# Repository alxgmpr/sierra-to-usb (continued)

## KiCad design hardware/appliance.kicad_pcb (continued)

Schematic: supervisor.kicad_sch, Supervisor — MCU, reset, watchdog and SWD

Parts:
C201, C202: 100nF; C_0603_1608Metric_Pad1.08x0.95mm_HandSolder; Rating 25V X7R +/-10%; 0603; Tolerance 10%; MPN CL10B104KA8NNNC; LCSC C1590
C203: 10uF; C_1206_3216Metric_Pad1.33x1.80mm_HandSolder; Rating 25V X7R +/-10%; bias margin reviewed; a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; Tolerance 10%; MPN CL31B106KBHNNNE; LCSC C89632
C204, C205: 100nF; C_0603_1608Metric_Pad1.08x0.95mm_HandSolder; Tolerance 10%; Voltage Rating 25V; MPN CL10B104KA8NNNC; LCSC C1590
J201: SWD TC2050; Tag-Connect_TC2050-IDC-FP_2x05_P1.27mm_Vertical; MPN TC2050-IDC
J202: WDT RUN jumper; Wuerth_61300211121_1x02_P2.54mm_Vertical; MPN 61300211121
R201, R202, R203: 10kR; R_0603_1608Metric_Pad0.98x0.95mm_HandSolder; Tolerance 1%; Power Rating 0.1W; MPN RC0603FR-0710KL; LCSC C98220
SW201: RESET; SW_SPST_TL3342; Contact Rating 12VDC 50mA; MPN TL3342F160QG; LCSC C2886898
U201: STM32G0B1CCT6; LQFP-48_7x7mm_P0.5mm; MPN STM32G0B1CCT6; LCSC C5270241
U202: TPS3828-33DBVR; SOT-23-5_HandSoldering; MPN TPS3828-33DBVR; LCSC C20032

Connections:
+3V3: C201.1, C202.1, C203.1, C204.1, J201.1 (VCC), R201.1, R203.1, U201.4 (VBAT), U201.5 (VREF+), U201.6 (VDD), U202.5 (V_{DD}); also elsewhere on the board
/Recovery and always-on supply/ETH_RESET_ASSERT: U201.8 (PF0); also elsewhere on the board
/Recovery and always-on supply/MODEM_OFF_ASSERT: U201.34 (PA10/PA12); also elsewhere on the board
/Recovery and always-on supply/MODEM_RESET_ASSERT: U201.33 (PA9/PA11); also elsewhere on the board
/Recovery and always-on supply/POWER_FAULT_N: U201.20 (PB1); also elsewhere on the board
/Recovery and always-on supply/SERVICE_RX: U201.14 (PA3); also elsewhere on the board
/Recovery and always-on supply/SERVICE_TX: U201.13 (PA2); also elsewhere on the board
/Recovery and always-on supply/Supervisor/MANUAL_RESET_N: R203.2, SW201.1, U202.3 (~MR)
/Recovery and always-on supply/Supervisor/MCU_NRST_N: C205.1, J201.10 (nRESET), R201.2, U201.10 (PF2), U202.1 (~RESET)
/Recovery and always-on supply/Supervisor/SWCLK: J201.4 (SWCLK), U201.36 (PA14)
/Recovery and always-on supply/Supervisor/SWDIO: J201.2 (SWDIO), U201.35 (PA13)
/Recovery and always-on supply/Supervisor/WDT_INPUT: J202.2, U202.4 (WDI)
/Recovery and always-on supply/Supervisor/WDT_KICK: J202.1, R202.1, U201.19 (PB0)
ADC_3V3_MAIN: U201.15 (PA4); also elsewhere on the board
ADC_5V_MAIN: U201.12 (PA1); also elsewhere on the board
ADC_AUX_12V: U201.11 (PA0); also elsewhere on the board
ADC_MODEM_ILM: U201.17 (PA6); also elsewhere on the board
ADC_MODEM_VCC: U201.16 (PA5); also elsewhere on the board
ADC_NTC_MODEM: U201.18 (PA7); also elsewhere on the board
ADC_NTC_POWER: U201.21 (PB2); also elsewhere on the board
GND: C201.2, C202.2, C203.2, C204.2, C205.2, J201.3 (GND), J201.5 (GND), J201.9 (GND), R202.2, SW201.2, U201.7 (VSS), U202.2 (GND); also elsewhere on the board
LED_FAULT_N: U201.39 (PD1); also elsewhere on the board
LED_PWR_N: U201.28 (PA8); also elsewhere on the board
LED_SYS_N: U201.37 (PA15); also elsewhere on the board
LED_WAN_N: U201.38 (PD0); also elsewhere on the board
MAIN3V3_GOOD: U201.44 (PB5); also elsewhere on the board
MAIN5V_GOOD: U201.46 (PB7); also elsewhere on the board
MCU_ETH_POWER_EN: U201.41 (PD3); also elsewhere on the board
MCU_HEALTH_IN: U201.1 (PC13); also elsewhere on the board
MCU_LINK_RX: U201.31 (PC7); also elsewhere on the board
MCU_LINK_TX: U201.30 (PC6); also elsewhere on the board
MCU_MAIN5V_EN: U201.45 (PB6); also elsewhere on the board
MCU_MODEM_POWER_EN: U201.40 (PD2); also elsewhere on the board
MCU_PROCESSOR_RECOVERY_ASSERT: U201.42 (PB3); also elsewhere on the board
MCU_PROCESSOR_RESET_ASSERT: U201.9 (PF1); also elsewhere on the board
MCU_PWRON_KICK: U201.43 (PB4); also elsewhere on the board
MODEM_BUCK_GOOD: U201.27 (PB15); also elsewhere on the board
MODEM_RAIL_GOOD: U201.25 (PB13); also elsewhere on the board
MODEM_SWITCH_GOOD: U201.26 (PB14); also elsewhere on the board
MON_ALERT_N: U201.2 (PC14); also elsewhere on the board
MON_I2C_SCL: U201.47 (PB8); also elsewhere on the board
MON_I2C_SDA: U201.48 (PB9); also elsewhere on the board
POE_BT_N: U201.24 (PB12); also elsewhere on the board
POE_TPH_N: U201.22 (PB10); also elsewhere on the board
POE_TPL_N: U201.23 (PB11); also elsewhere on the board

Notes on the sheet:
100nF at VDD/VREF; 10uF local bulk. No external clock required for UART/GPIO supervision.
PROGRAMMING / MANUAL RECOVERY
SUPERVISOR MCU — CONTROL ONLY
PF2 / pin 10 MUST remain NRST via option bytes. Internal BOR and IWDG enabled by protected boot firmware. PA2/PA3: USART2 AF1; PA13/PA14: SWD. UART is service only; no modem AT transport selected. Two signed app slots + protected loader planned; not implemented.
Fit RUN jumper for unattended use. Remove only for physical SWD service. WDI floats only with jumper removed.
VTref only; debugger must not power the target. Leave debug unlocked until signed-update recovery is proven. No USB data path through this MCU.
1.6s nominal watchdog; 2.93V threshold; 200ms nominal reset. Open-drain RESET directly shares MCU NRST with SWD. Verify NRST low-voltage margin across temperature before release.
EXTERNAL WATCHDOG + BROWNOUT

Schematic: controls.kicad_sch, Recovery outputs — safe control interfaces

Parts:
Q301, Q302, Q303: MMBT3904,215; SOT-23_Handsoldering; MPN MMBT3904,215
R301, R303, R305: 10kR; R_0603_1608Metric_Pad0.98x0.95mm_HandSolder; Tolerance 1%; Power Rating 0.1W; MPN RC0603FR-0710KL; LCSC C98220
R302, R304, R306, R307, R308: 100kR; R_0603_1608Metric_Pad0.98x0.95mm_HandSolder; Tolerance 1%; Power Rating 0.1W; MPN RC0603FR-07100KL; LCSC C14675

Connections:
/Recovery and always-on supply/ETH_RESET_ASSERT: R305.1; also elsewhere on the board
/Recovery and always-on supply/MODEM_OFF_ASSERT: R303.1; also elsewhere on the board
/Recovery and always-on supply/MODEM_RESET_ASSERT: R301.1; also elsewhere on the board
ETH_PERST_N: Q303.3 (C); also elsewhere on the board
GND: Q301.2 (E), Q302.2 (E), Q303.2 (E), R302.2, R304.2, R306.2, R307.2, R308.2; also elsewhere on the board
MCU_ETH_POWER_EN: R308.1; also elsewhere on the board
MCU_MODEM_POWER_EN: R307.1; also elsewhere on the board
MODEM_OFF_N: Q302.3 (C); also elsewhere on the board
MODEM_RESET_N: Q301.3 (C); also elsewhere on the board
unnamed: Q301.1 (B), R301.2, R302.1
unnamed: Q302.1 (B), R303.2, R304.1
unnamed: Q303.1 (B), R305.2, R306.1

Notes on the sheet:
INTEGRATION LIMITS
OPEN-COLLECTOR RESET / OFF — NO EXTERNAL PULL-UP TO ALWAYS-ON RAIL
POWER ENABLES — DEFAULT OFF ON MCU RESET
HIGH input asserts LOW output. Target pull-up / timing is profile-specific.
Reset outputs tolerate target pull-ups without sourcing voltage into an unpowered target. Maximum target sink current allocation: 1mA; verify low threshold with exact load. MODEM_OFF_N connects to FULL_CARD_POWER_OFF# only with a switched target-rail pull-up. Without that pull-up, the module remain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
Connect only to documented 3.3V-compatible enable inputs. The regulators / eFuses are NOT captured in this milestone.

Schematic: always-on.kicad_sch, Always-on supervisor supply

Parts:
C401: 10uF; C_1206_3216Metric_Pad1.33x1.80mm_HandSolder; Tolerance 10%; Voltage Rating 50V; MPN CL31B106KBHNNNE; LCSC C89632
C402, C403: 22uF; C_1210_3225Metric_Pad1.33x2.70mm_HandSolder; Tolerance 10%; Voltage Rating 25V; MPN CL32B226KAJNNNE; LCSC C309062
L401: 10uH; L_Coilcraft_LPS4018; MPN LPS4018-103MRC; LCSC C6127589
R401: 100kR; R_0603_1608Metric_Pad0.98x0.95mm_HandSolder; Tolerance 1%; Power Rating 0.1W; MPN RC0603FR-07100KL; LCSC C14675
U401: TPS62177DQCR; WSON-10-1EP_2x3mm_P0.5mm_EP0.84x2.4mm_ThermalVias; MPN TPS62177DQCR; LCSC C91241

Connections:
+3V3: C402.1, C403.1, L401.2, R401.1, U401.8 (~SLEEP), U401.10 (VOS); also elsewhere on the board
/Recovery and always-on supply/POWER_FAULT_N: R401.2, U401.7 (PG); also elsewhere on the board
GND: C401.2, C402.2, C403.2, U401.1 (PGND), U401.4 (NC), U401.5 (FB), U401.6 (AGND), U401.11 (PAD); also elsewhere on the board
ISO_12V: C401.1, U401.2 (VIN), U401.3 (EN); also elsewhere on the board
unnamed: L401.1, U401.9 (SW)

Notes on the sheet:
Independent supervisor supply
DRAFT: isolated 12V input; 3.3V / 0.5A output. No connection to raw PoE. EN tied to input; SLEEP tied to 3.3V for normal operation. Always on while the isolated input is present; downstream cuts must not gate this rail.
TI SLVSB35C, Figure 8 / Tables 2-3. 10uH + 2x22uF nominal. Capacitor DC bias, complete rail load and layout review remain open. Route VOS as Kelvin sense after L401; join AGND / PGND / exposed pad locally.

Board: 6 copper layers, 816 parts (202 on the bottom side), 426 nets, no tracks yet.

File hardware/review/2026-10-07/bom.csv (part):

Reference,Value,MPN,Manufacturer,Footprint,Default Assembly,Profile Rule,Datasheet,Release
J101,3.3V RAIL TEST,61300211121,Wuerth Elektronik,Recovery:Wuerth_61300211121_1x02_P2.54mm_Vertical,Fit,,https://www.we-online.com/components/products/datasheet/6130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,Engineering inventory; modem/footprint/electrical qualification pending
J102,CONTROL BOUNDARY,61301011121,Wuerth Elektronik,Recovery:Wuerth_61301011121_1x10_P2.54mm_Vertical,Fit,,https://www.we-online.com/components/products/datasheet/6130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,Engineering inventory; modem/footprint/electrical qualification pending
Q301,"MMBT3904,215","MMBT3904,215",Nexperia,Package_TO_SOT_SMD:SOT-23_Handsoldering,Fit,,https://assets.nexperia.com/documents/data-sheet/MMBT3904.pdf,Engineering inventory; modem/footprint/electrical qualification pending
Q302,"MMBT3904,215","MMBT3904,215",Nexperia,Package_TO_SOT_SMD:SOT-23_Handsoldering,Fit,,https://assets.nexperia.com/documents/data-sheet/MMBT3904.pdf,Engineering inventory; modem/footprint/electrical qualification pending
Q303,"MMBT3904,215","MMBT3904,215",Nexperia,Package_TO_SOT_SMD:SOT-23_Handsoldering,Fit,,https://assets.nexperia.com/documents/data-sheet/MMBT3904.pdf,Engineering inventory; modem/footprint/electrical qualification pending
R301,10kR,RC0603FR-0710KL,Yageo,Resistor_SMD:R_0603_1608Metric_Pad0.98x0.95mm_HandSolder,Fit,,https://www.yageo.com/upload/media/product/productsearch/dat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,Engineering inventory; modem/footprint/electrical qualification pending
R302,100kR,RC0603FR-07100KL,Yageo,Resistor_SMD:R_0603_1608Metric_Pad0.98x0.95mm_HandSolder,Fit,,https://www.yageo.com/upload/media/product/productsearch/dat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,Engineering inventory; modem/footprint/electrical qualification pending
R303,10kR,RC0603FR-0710KL,Yageo,Resistor_SMD:R_0603_1608Metric_Pad0.98x0.95mm_HandSolder,Fit,,https://www.yageo.com/upload/media/product/productsearch/dat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,Engineering inventory; modem/footprint/electrical qualification pending
R304,100kR,RC0603FR-07100KL,Yageo,Resistor_SMD:R_0603_1608Metric_Pad0.98x0.95mm_HandSolder,Fit,,https://www.yageo.com/upload/media/product/productsearch/dat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,Engineering inventory; modem/footprint/electrical qualification pending
R305,10kR,RC0603FR-0710KL,Yageo,Resistor_SMD:R_0603_1608Metric_Pad0.98x0.95mm_HandSolder,Fit,,https://www.yageo.com/upload/media/product/productsearch/dat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,Engineering inventory; modem/footprint/electrical qualification pending
R306,100kR,RC0603FR-07100KL,Yageo,Resistor_SMD:R_0603_1608Metric_Pad0.98x0.95mm_HandSolder,Fit,,https://www.yageo.com/upload/media/product/productsearch/dat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,Engineering inventory; modem/footprint/electrical qualification pending
R307,100kR,RC0603FR-07100KL,Yageo,Resistor_SMD:R_0603_1608Metric_Pad0.98x0.95mm_HandSolder,Fit,,https://www.yageo.com/upload/media/product/productsearch/dat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,Engineering inventory; modem/footprint/electrical qualification pending
R308,100kR,RC0603FR-07100KL,Yageo,Resistor_SMD:R_0603_1608Metric_Pad0.98x0.95mm_HandSolder,Fit,,https://www.yageo.com/upload/media/product/productsearch/dat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,Engineering inventory; modem/footprint/electrical qualification pending
C401,4.7uF / 50V,CL31B475KBHNNNE,Samsung Electro-Mechanics,Capacitor_SMD:C_1206_3216Metric_Pad1.33x1.80mm_HandSolder,Fit,,,Engineering inventory; modem/footprint/electrical qualification pending
C402,22uF / 25V,CL32B226KAJNNNE,Samsung Electro-Mechanics,Capacitor_SMD:C_1210_3225Metric_Pad1.33x2.70mm_HandSolder,Fit,,,Engineering inventory; modem/footprint/electrical qualification pending
C403,22uF / 25V,CL32B226KAJNNNE,Samsung Electro-Mechanics,Capacitor_SMD:C_1210_3225Metric_Pad1.33x2.70mm_HandSolder,Fit,,,Engineering inventory; modem/footprint/electrical qualification pending
L401,10uH,LPS4018-103MRC,Coilcraft,Inductor_SMD:L_Coilcraft_LPS4018,Fit,,https://www.coilcraft.com/getmedia/31b05c96-4c4c-4498-8dbb-f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,Engineering inventory; modem/footprint/electrical qualification pending
R401,100kR,RC0603FR-07100KL,Yageo,Resistor_SMD:R_0603_1608Metric_Pad0.98x0.95mm_HandSolder,Fit,,,Engineering inventory; modem/footprint/electrical qualification pending
U401,TPS62177DQCR,TPS62177DQCR,Texas Instruments,Package_SON:WSON-10-1EP_2x3mm_P0.5mm_EP0.84x2.4mm_ThermalVias,Fit,,https://www.ti.com/lit/ds/symlink/tps62175.pdf,Engineering inventory; modem/footprint/electrical qualification pending
C201,100nF,CL10B104KA8NNNC,Samsung Electro-Mechanics,Capacitor_SMD:C_0603_1608Metric_Pad1.08x0.95mm_HandSolder,Fit,,https://product.samsungsem.com/mlcc/CL10B104KA8NNN.do,Engineering inventory; modem/footprint/electrical qualification pending
C202,100nF,CL10B104KA8NNNC,Samsung Electro-Mechanics,Capacitor_SMD:C_0603_1608Metric_Pad1.08x0.95mm_HandSolder,Fit,,https://product.samsungsem.com/mlcc/CL10B104KA8NNN.do,Engineering inventory; modem/footprint/electrical qualification pending
C203,10uF,CL31B106KAHNNNE,Samsung Electro-Mechanics,Capacitor_SMD:C_1206_3216Metric_Pad1.33x1.80mm_HandSolder,Fit,,https://product.samsungsem.com/mlcc/CL31B106KAHNNN.do,Engineering inventory; modem/footprint/electrical qualification pending
C204,100nF,CL10B104KA8NNNC,Samsung Electro-Mechanics,Capacitor_SMD:C_0603_1608Metric_Pad1.08x0.95mm_HandSolder,Fit,,https://product.samsungsem.com/mlcc/CL10B104KA8NNN.do,Engineering inventory; modem/footprint/electrical qualification pending
C205,100nF,CL10B104KA8NNNC,Samsung Electro-Mechanics,Capacitor_SMD:C_0603_1608Metric_Pad1.08x0.95mm_HandSolder,Fit,,https://product.samsungsem.com/mlcc/CL10B104KA8NNN.do,Engineering inventory; modem/footprint/electrical qualification pending
J201,SWD / recovery,61300611121,Wuerth Elektronik,Recovery:Wuerth_61300611121_1x06_P2.54mm_Vertical,Fit,,https://www.we-online.com/components/products/datasheet/6130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,Engineering inventory; modem/footprint/electrical qualification pending
J202,WDT RUN jumper,61300211121,Wuerth Elektronik,Recovery:Wuerth_61300211121_1x02_P2.54mm_Vertical,Fit,,https://www.we-online.com/components/products/datasheet/6130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,Engineering inventory; modem/footprint/electrical qualification pending
R201,10kR,RC0603FR-0710KL,Yageo,Resistor_SMD:R_0603_1608Metric_Pad0.98x0.95mm_HandSolder,Fit,,https://www.yageo.com/upload/media/product/productsearch/dat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,Engineering inventory; modem/footprint/electrical qualification pending
R202,10kR,RC0603FR-0710KL,Yageo,Resistor_SMD:R_0603_1608Metric_Pad0.98x0.95mm_HandSolder,Fit,,https://www.yageo.com/upload/media/product/productsearch/dat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,Engineering inventory; modem/footprint/electrical qualification pending
R203,10kR,RC0603FR-0710KL,Yageo,Resistor_SMD:R_0603_1608Metric_Pad0.98x0.95mm_HandSolder,Fit,,https://www.yageo.com/upload/media/product/productsearch/dat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,Engineering inventory; modem/footprint/electrical qualification pending
SW201,RESET,TL3342F160QG,E-Switch,Button_Switch_SMD:SW_SPST_TL3342,Fit,,https://configured-product-images.s3.amazonaws.com/2D/specs/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,Engineering inventory; modem/footprint/electrical qualification pending
U201,STM32G0B1CCT6,STM32G0B1CCT6,STMicroelectronics,Package_QFP:LQFP-48_7x7mm_P0.5mm,Fit,,https://www.st.com/resource/en/datasheet/stm32g0b1cc.pdf,Engineering inventory; modem/footprint/electrical qualification pending
U202,TPS3828-33DBVR,TPS3828-33DBVR,Texas Instruments,Package_TO_SOT_SMD:SOT-23-5_HandSoldering,Fit,,https://www.ti.com/lit/ds/symlink/tps3828.pdf,Engineering inventory; modem/footprint/electrical qualification pending
C501,22uF / 25V,CL32B226KAJNNNE,Samsung Electro-Mechanics,Capacitor_SMD:C_1210_3225Metric_Pad1.33x2.70mm_HandSolder,Fit,,,Engineering inventory; modem/footprint/electrical qualification pending
C502,22uF / 25V,CL32B226KAJNNNE,Samsung Electro-Mechanics,Capacitor_SMD:C_1210_3225Metric_Pad1.33x2.70mm_HandSolder,Fit,,,Engineering inventory; modem/footprint/electrical qualification pending
C503,22uF / 25V,CL32B226KAJNNNE,Samsung Electro-Mechanics,Capacitor_SMD:C_1210_3225Metric_Pad1.33x2.70mm_HandSolder,Fit,,,Engineering inventory; modem/footprint/electrical qualification pending
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
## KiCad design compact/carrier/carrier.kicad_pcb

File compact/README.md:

# Compact USB-C modem carrier

The current design is [carrier/carrier.kicad_pro](carrier/carrier.kicad_pro), with a complete10-page schematic and a deliberately placed, entirely unrouted110×100mm PCB. Open it in KiCad10.99 or a compatible newer build. The original root project is preserved.

Start with [handoff artifacts](carrier/HANDOFF.md), [review and open gates](carrier/REVIEW.md), and [routing guide](carrier/ROUTING.md). The carrier has159 placed schematic components, zero ERC findings, zero parity findings and zero placement DRC violations;446 unconnected findings are intentional. No tracks, vias, filled copper or production Gerbers were created.

The design uses one USB-C port with3A current authorization, automatic USB3 orientation, module-powered nano-SIM, fixed vendor profiles, accessible controls and four edge SMA breakouts. Scope is EM9190 sub-6 and document-qualified RM520N-GL V1.0; RM551E is excluded. macOS networking remains a separate firmware/hardware test.

The4.0V input design has only69.8mW of calculated surplus under stated hot-loss allocations. It is a placement-stage prototype, not a fabrication-ready or bench-qualified design. Exact buck/socket sourcing, accepted stackup, CC configuration/readback, actual module/cooler/coax fit and all electrical/thermal/interface bench tests remain explicit gates in the review.

`energy-storage.kicad_sch` and the earlier TPS259470L/LTC3128/TPS62816 analyses are historical rejected candidates. Their passing subset checks do not apply to the current carrier. Current power calculations and source/compatibility records are under `review/`; final carrier checks and artifacts are under `carrier/build/`.

Generators use SHA-256 preflight guards. Preserve all generated/manual work; reconcile changes into generator sources rather than refreshing hashes to bypass a conflict. Once manual PCB routing starts, do not regenerate over it. Reproduction instructions are in the handoff index.

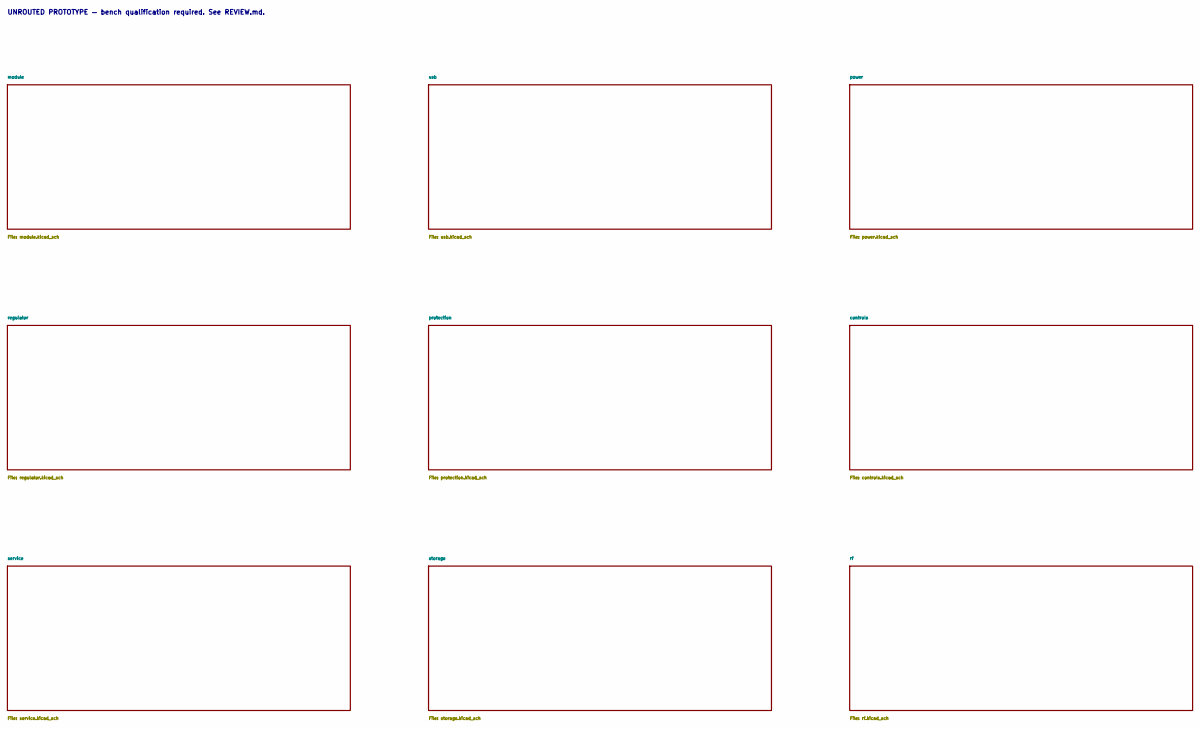
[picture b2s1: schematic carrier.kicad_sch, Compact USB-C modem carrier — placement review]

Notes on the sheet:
UNROUTED PROTOTYPE — bench qualification required. See REVIEW.md.

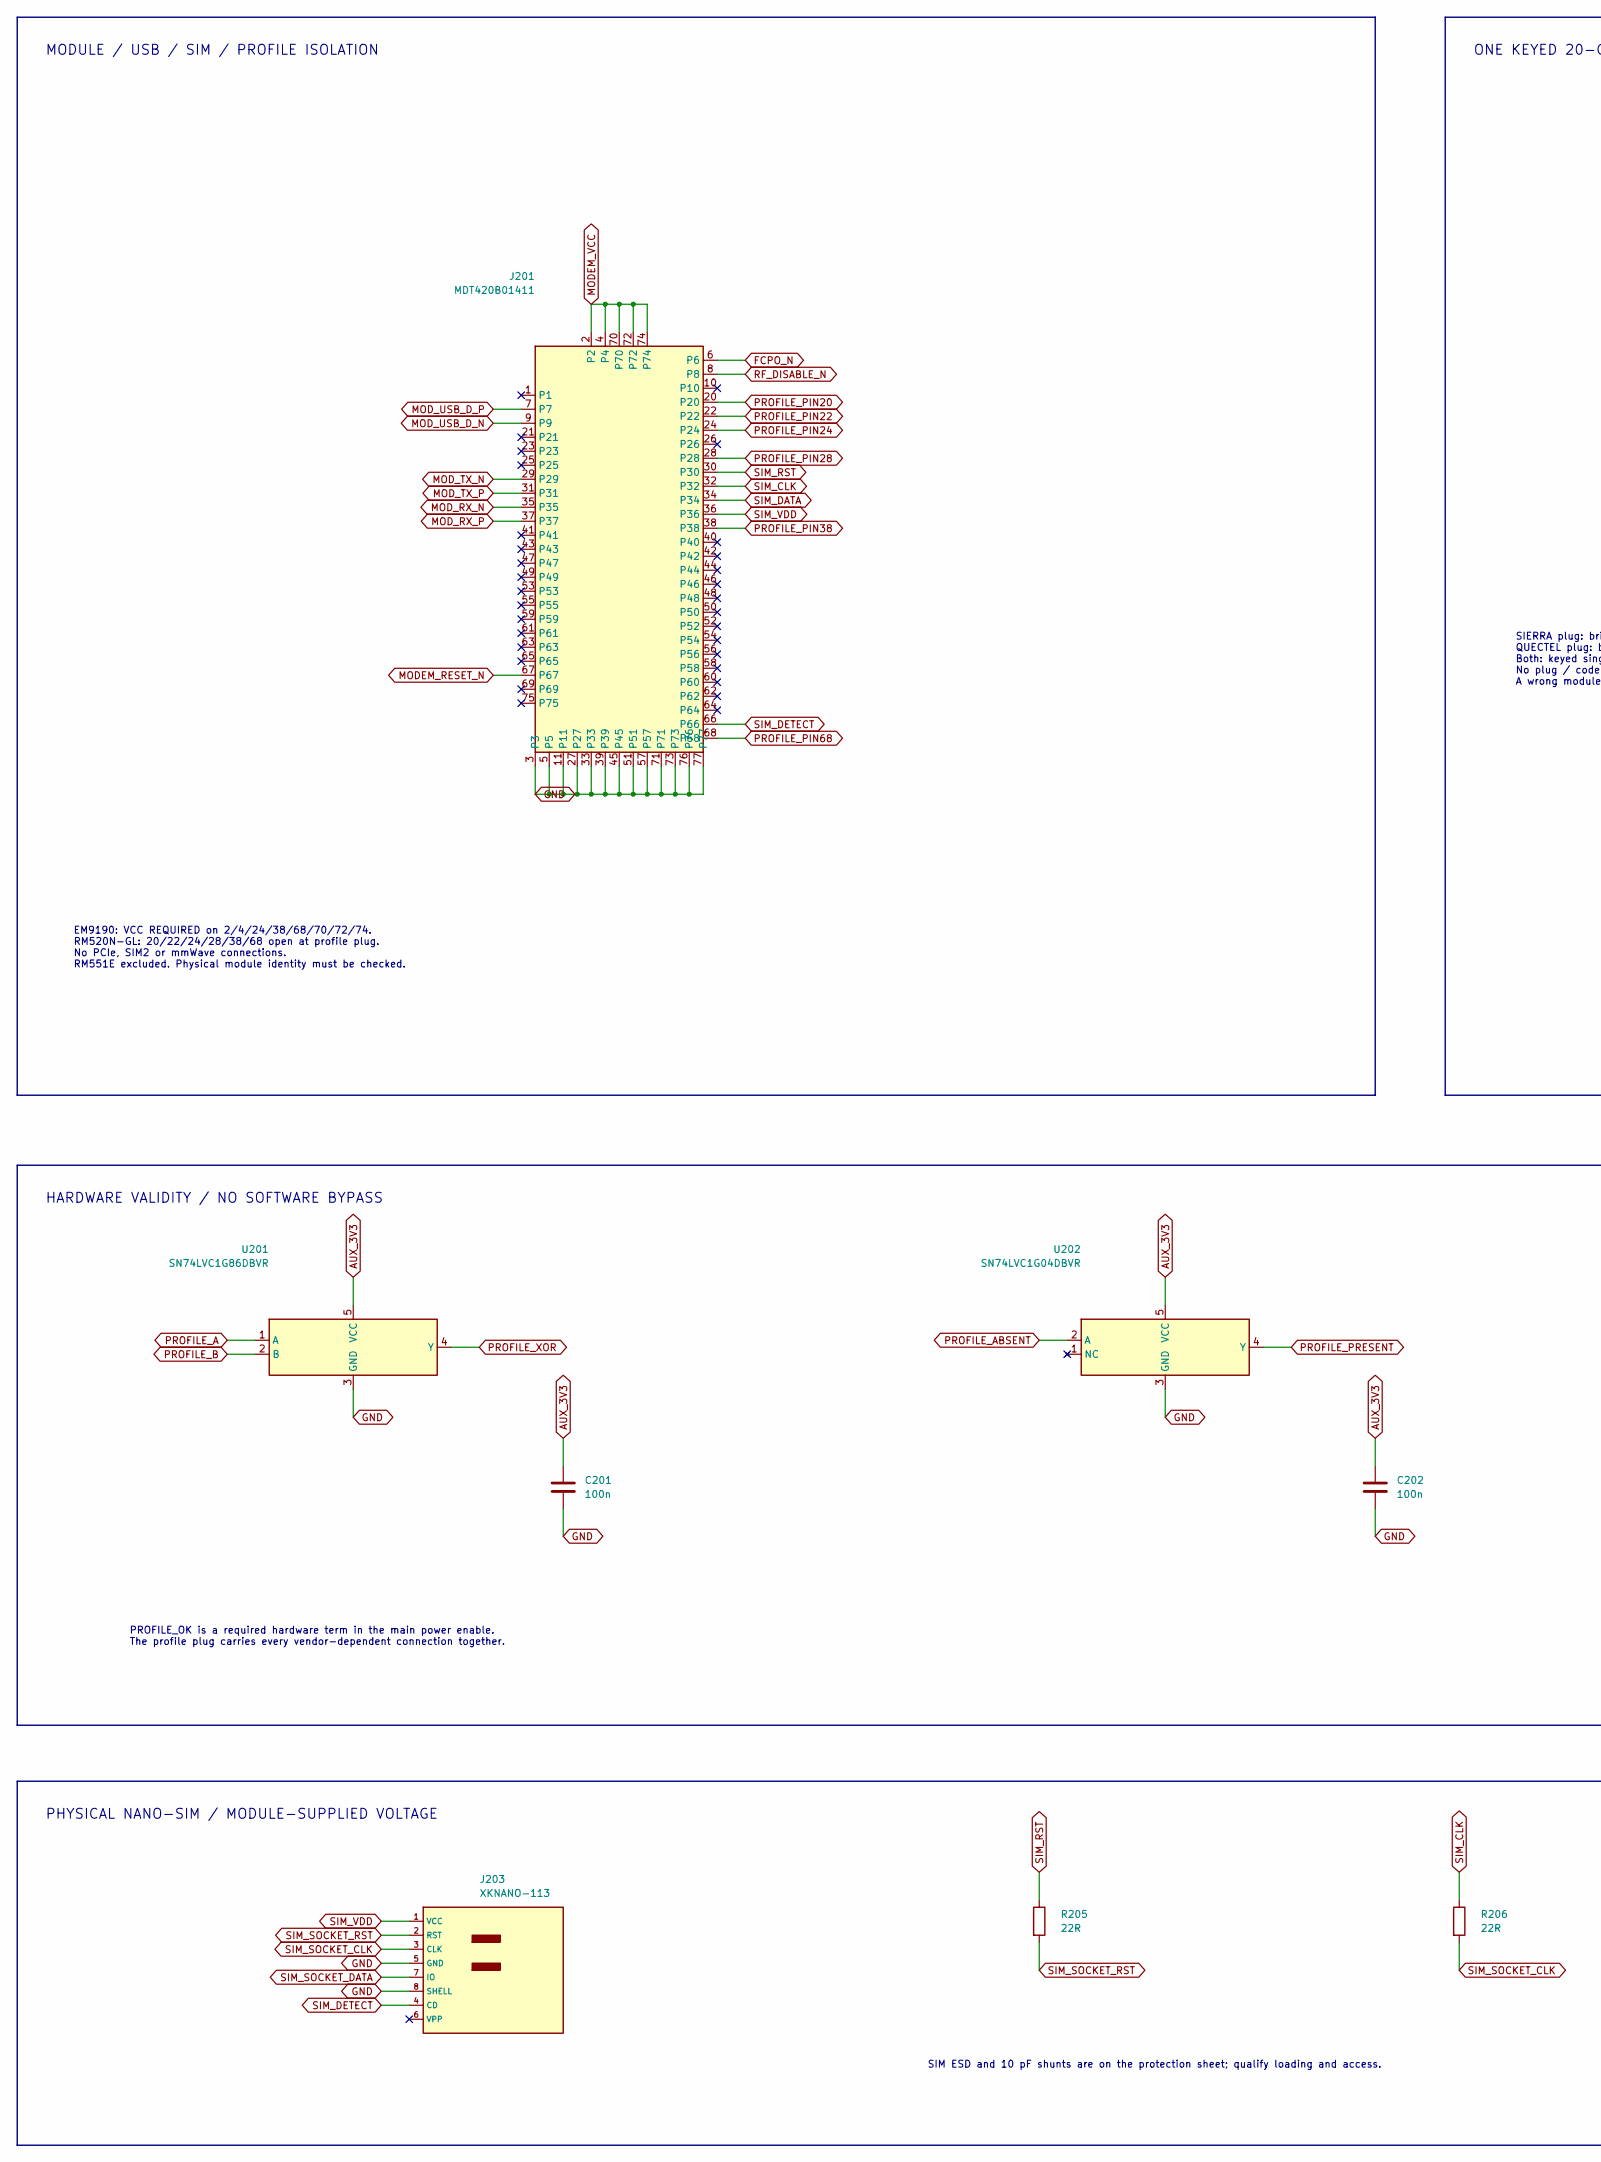
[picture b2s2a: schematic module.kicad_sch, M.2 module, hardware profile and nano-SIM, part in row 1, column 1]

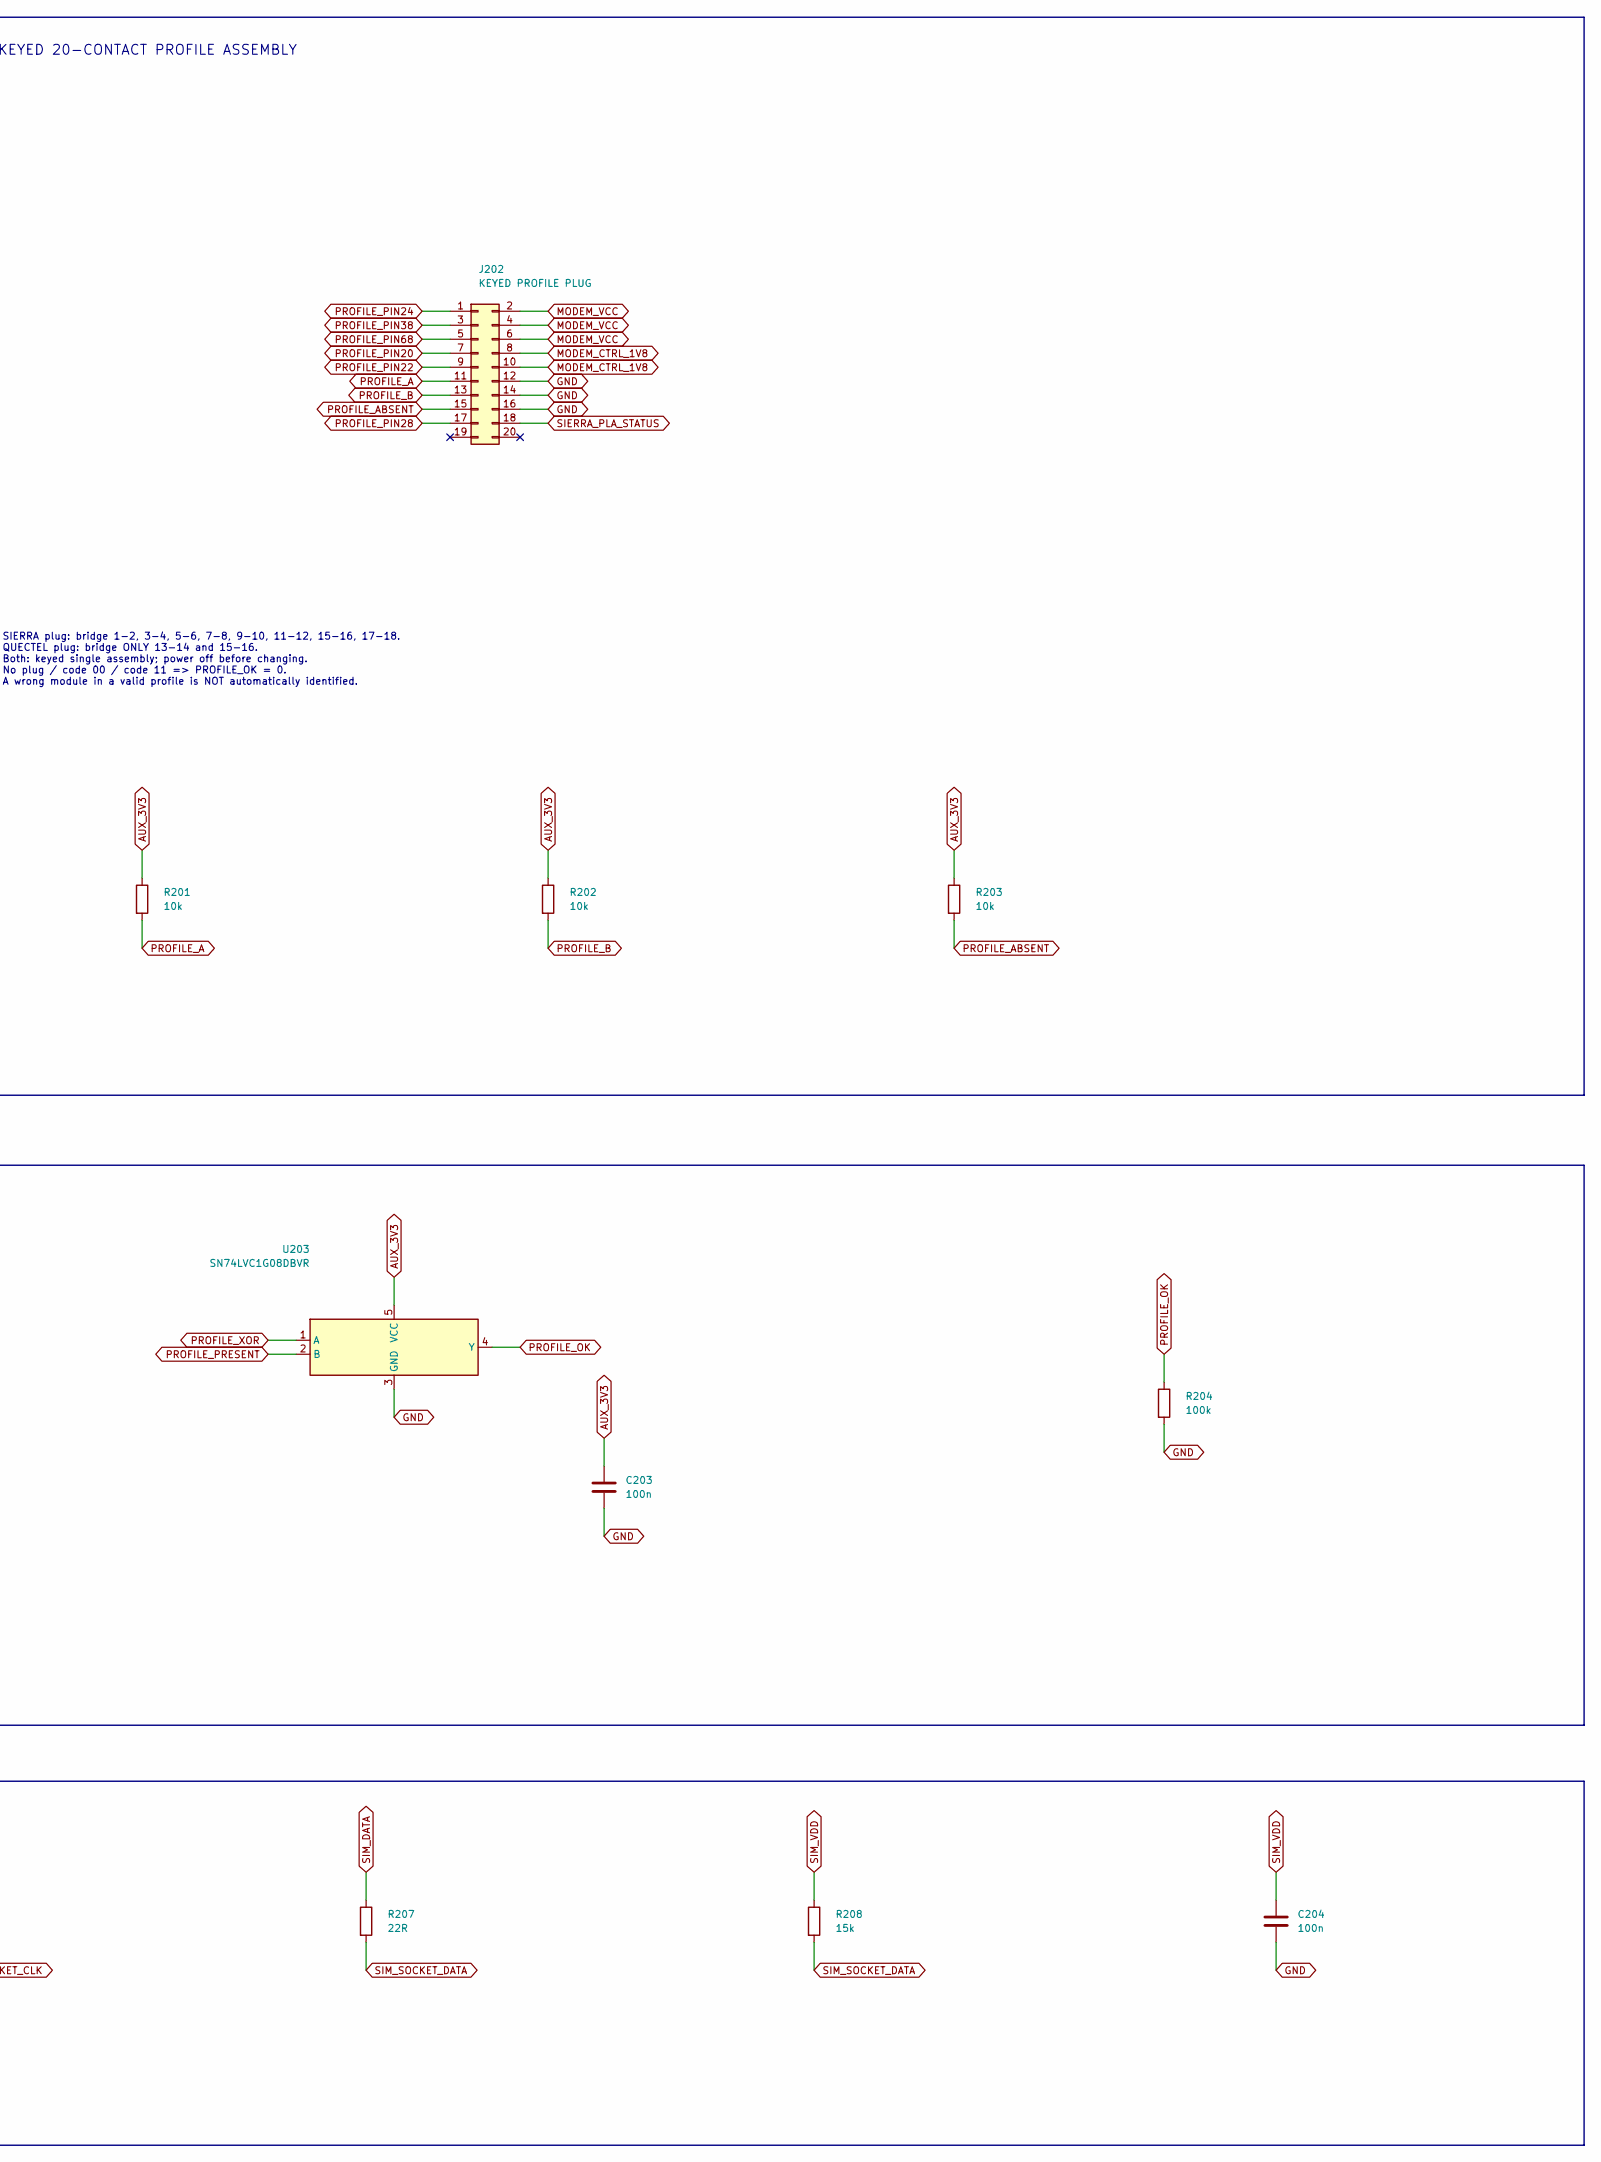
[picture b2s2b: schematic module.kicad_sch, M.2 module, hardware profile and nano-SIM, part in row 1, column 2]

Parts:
C201, C202, C203, C204: 100n; C_0805_2012Metric; MPN C2012X7R1H104K085AA
J201: MDT420B01411; M2_B_Amphenol_MDT420_1A; MPN MDT420B01411
J202: KEYED PROFILE PLUG; IDC_3M_N2520_6002_RB; MPN N2520-6002-RB
J203: XKNANO-113; NanoSIM_XKB_XKNANO-113; MPN XKNANO-113; LCSC C381071
R201, R202, R203: 10k; R_0603_1608Metric; MPN RC0603FR-0710KL
R204: 100k; R_0603_1608Metric; MPN RC0603FR-07100KL
R205, R206, R207: 22R; R_0603_1608Metric; MPN ERJ-3EKF22R0V
R208: 15k; R_0603_1608Metric; MPN RC0603FR-0715KL
U201: SN74LVC1G86DBVR; SOT-23-5; MPN SN74LVC1G86DBVR
U202: SN74LVC1G04DBVR; SOT-23-5; MPN SN74LVC1G04DBVR
U203: SN74LVC1G08DBVR; SOT-23-5; MPN SN74LVC1G08DBVR

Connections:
AUX_3V3: C201.1, C202.1, C203.1, R201.1, R202.1, R203.1, U201.5 (VCC), U202.5 (VCC), U203.5 (VCC); also elsewhere on the board
FCPO_N: J201.6; also elsewhere on the board
GND: C201.2, C202.2, C203.2, C204.2, J201.3, J201.5, J201.11, J201.27, J201.33, J201.39, J201.45, J201.51, J201.57, J201.71, J201.73, J201.76, J201.77, J202.12, J202.14, J202.16, J203.5 (GND), J203.8 (SHELL), R204.2, U201.3 (GND), U202.3 (GND), U203.3 (GND); also elsewhere on the board
MODEM_CTRL_1V8: J202.8, J202.10; also elsewhere on the board
MODEM_RESET_N: J201.67; also elsewhere on the board
MODEM_VCC: J201.2, J201.4, J201.70, J201.72, J201.74, J202.2, J202.4, J202.6; also elsewhere on the board
MOD_RX_N: J201.35; also elsewhere on the board
MOD_RX_P: J201.37; also elsewhere on the board
MOD_TX_N: J201.29; also elsewhere on the board
MOD_TX_P: J201.31; also elsewhere on the board
MOD_USB_D_N: J201.9; also elsewhere on the board
MOD_USB_D_P: J201.7; also elsewhere on the board
PROFILE_A: J202.11, R201.2, U201.1 (A)
PROFILE_ABSENT: J202.15, R203.2, U202.2 (A)
PROFILE_B: J202.13, R202.2, U201.2 (B)
PROFILE_OK: R204.1, U203.4 (Y); also elsewhere on the board
PROFILE_PIN20: J201.20, J202.7
PROFILE_PIN22: J201.22, J202.9
PROFILE_PIN24: J201.24, J202.1
PROFILE_PIN28: J201.28, J202.17
PROFILE_PIN38: J201.38, J202.3
PROFILE_PIN68: J201.68, J202.5
PROFILE_PRESENT: U202.4 (Y), U203.2 (B)
PROFILE_XOR: U201.4 (Y), U203.1 (A)
RF_DISABLE_N: J201.8; also elsewhere on the board
SIERRA_PLA_STATUS: J202.18; also elsewhere on the board
SIM_CLK: J201.32, R206.1
SIM_DATA: J201.34, R207.1
SIM_DETECT: J201.66, J203.4 (CD)
SIM_RST: J201.30, R205.1
SIM_SOCKET_CLK: J203.3 (CLK), R206.2; also elsewhere on the board
SIM_SOCKET_DATA: J203.7 (IO), R207.2, R208.2; also elsewhere on the board
SIM_SOCKET_RST: J203.2 (RST), R205.2; also elsewhere on the board
SIM_VDD: C204.1, J201.36, J203.1 (VCC), R208.1; also elsewhere on the board

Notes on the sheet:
MODULE / USB / SIM / PROFILE ISOLATION
EM9190: VCC REQUIRED on 2/4/24/38/68/70/72/74. RM520N-GL: 20/22/24/28/38/68 open at profile plug. No PCIe, SIM2 or mmWave connections. RM551E excluded. Physical module identity must be checked.
ONE KEYED 20-CONTACT PROFILE ASSEMBLY
SIERRA plug: bridge 1-2, 3-4, 5-6, 7-8, 9-10, 11-12, 15-16, 17-18. QUECTEL plug: bridge ONLY 13-14 and 15-16. Both: keyed single assembly; power off before changing. No plug / code 00 / code 11 => PROFILE_OK = 0. A wrong module in a valid profile is NOT automatically identified.
HARDWARE VALIDITY / NO SOFTWARE BYPASS
PROFILE_OK is a required hardware term in the main power enable. The profile plug carries every vendor-dependent connection together.
PHYSICAL NANO-SIM / MODULE-SUPPLIED VOLTAGE
SIM ESD and 10 pF shunts are on the protection sheet; qualify loading and access.
